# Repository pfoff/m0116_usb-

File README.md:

# m0116_usb
[![CC BY-NC-SA 4.0][cc-by-nc-sa-shield]][cc-by-nc-sa]

**[Deutsch](#deutsch) | [English](#english)**

## Deutsch

### Dieses Projekt ist abgeschlossen und wird nicht mehr aktualisiert.
Wir sind absolute Anfänger und wollen eine Platine für einige unserer M0118
bauen, irgendwann mit Unterstützung für ANSI-Belegung mit AEK-Tastenkappen.
Hilfe und Tipps sind willkommen.

### Wireless-TrackPoint-Revision (Branch `wireless-trackpoint`)

In Arbeit: Der ursprüngliche ATmega32A/V-USB-Controller wird durch einen
gesockelten **nice!nano v2** mit **ZMK** ersetzt, dazu ein PS/2-TrackPoint
und ein LiPo-Akku. Platinenkontur, Schalterpositionen, die 5×18-Matrix und
die Befestigungslöcher bleiben unverändert. Designnotizen, Pinbelegung und
offene Punkte: [docs/wireless-trackpoint-design.md](docs/wireless-trackpoint-design.md)
(englisch).

- `m0116_usb.kicad_sch` – Matrix (unverändert) plus zwei Unterblätter:
  - `controller.kicad_sch` – nice!nano, 3× 74HC595 als Spaltentreiber, LiPo,
    dauerhaft aktiver LDO, TrackPoint-Stecker
  - `usb_daughterboard.kicad_sch` – USB-C-Durchführung auf dem abbrechbaren
    Tab in der hinteren ADB-Aussparung, für Kabelbetrieb und Laden
- `m0116_wireless.kicad_sym` – Projekt-Symbolbibliothek (nice!nano v2)
- `tools/` – Hilfsskripte für das Makefile

Benötigt KiCad 7 (`kicad-cli` und das `pcbnew`-Python-Modul des
System-Pythons). Einmal `git submodule update --init` ausführen, um die
Footprint-Bibliotheken zu holen.

| Befehl | Was er macht |
|---|---|
| `make check` | Netzliste exportieren und die vorgesehenen Verbindungen prüfen |
| `make pcb-update` | Platine ohne GUI aus dem Schaltplan aktualisieren (Pcbnew vorher schließen) |
| `make pcb-check` | Ungeroutete Verbindungen Netz für Netz auflisten |
| `make pdf` | Schaltplan als PDF in `build/` |
| `make gerbers` | Gerber- und Bohrdateien, gezippt in `build/` |
| `make dsn` | Specctra-DSN der Tastenmatrix für Freerouting, in `build/` |
| `make dsn-continue` | DSN mit den vorhandenen Leiterbahnen, Freerouting ergänzt nur die offenen Verbindungen |
| `make clean` | `build/` löschen |

Die Schalter-Footprints sind MX/Alps-Hybride (`MX_Alps_Hybrid:MX-1U-NoLED`);
MX82 ist ein optionaler mittiger MX-Leertastenschalter parallel zum
außermittigen Alps-Leertastenschalter MX73 (nur einen der beiden bestücken).
Die Matrix wird mit Freerouting geroutet: `make dsn`, die DSN routen, dann
ersetzt `/usr/bin/python3 tools/import_ses.py <board> <datei.ses>` die
Leiterbahnen aller Netze aus der Session. Bei einem Teilergebnis
`make dsn-continue` ausführen (GND wird dort als Leiterbahn geroutet, damit
Inseln der Massefläche keine offenen Pads verstecken), routen und erneut
importieren; `/usr/bin/python3 tools/stitch_gnd.py <board>` setzt Vias von
GND-Inseln zur Hauptfläche, wo sich beide Lagen überlappen. Die exportierte
Kontur wird um 0,35 mm verkleinert und die Bohrungen vergrößert, weil
Freerouting nur 0,2 mm Abstand zur Kante hält und KiCad 0,5 mm prüft. Die
Netze der USB-Tochterplatine fehlen in der DSN (enge USB-C-Pads) und werden
von Hand geroutet. Die Frage von Freerouting, eine `.rules`-Datei zu
importieren, mit „Nein“ beantworten: Sie überschreibt die Regeln der neuen
DSN.

#### TKL-Variante (ohne Ziffernblock)

`m0116_tkl.*` wird per Skript aus der großen Platine erzeugt, Änderungen
lassen sich also übertragen: `make tkl-sch` erzeugt die Schaltpläne neu,
`make tkl-pcb` baut die Platine neu (überschreibt `m0116_tkl.kicad_pcb`).
Die anderen Targets nehmen `PROJECT=m0116_tkl`. Die Platine endet nach
Backspace/Return/Pfeiltasten mit der originalen rechten Kontur, um 94,43 mm
nach links verschoben; U4/C5 entfallen (14 Spalten), die rechte
Plattenschraube wandert mit der Kontur und muss in die gekürzte Platte
gebohrt werden.

`make pcb-update` platziert neue Footprints nur beim ersten Anlegen nach
`tools/placement.json`, manuelle Platzierung in Pcbnew bleibt also erhalten.

Stand: Schaltplan fertig (ERC sauber). Die TKL-Platine ist bis auf zwei
Verbindungen autogeroutet; die große Platine muss noch neu geroutet werden.
Der Tab der Tochterplatine muss angepasst werden, sobald die hintere
ADB-Aussparung des Gehäuses ausgemessen ist. Offene Schritte, für
KiCad-Einsteiger beschrieben: [TODO.md](TODO.md) (englisch).

### Originaldesign

Die folgenden Abschnitte beschreiben das ursprüngliche Design.

QMK-kompatible Drop-in-Ersatzplatine für den Apple M0116. Die Platine ist
komplett mit THT-Bauteilen aufgebaut, um einen etwas „vintage“ Look zu
behalten, und verwendet den ATmega32A im 40-poligen DIP-Gehäuse. (Hinweis
der Wireless-Revision: Der Controller sitzt in der Leiste hinter der
Zahlenreihe; die Bemerkung zur Leertaste in der englischen Fassung stammt
aus dem M0110a-Projekt.)

Stückliste (Partslist) und Bilder: siehe unten im englischen Teil, die
Tabelle ist sprachunabhängig.

## English
### This project is completed and will not get updated anymore.
We are complete beginners and want to build a pcb for some of our m0118s, eventually with support for ansi keymap, by using some aek keycaps. 
Any help or tips appreciated

### Wireless TrackPoint revision (branch `wireless-trackpoint`)

Work in progress: the original ATmega32A/V-USB controller is replaced by a
socketed **nice!nano v2** running **ZMK**, with a PS/2 TrackPoint and LiPo
battery. Board outline, switch positions, the 5x18 matrix and the mounting
holes stay unchanged. Design notes, pin assignment and open points:
[docs/wireless-trackpoint-design.md](docs/wireless-trackpoint-design.md).

- `m0116_usb.kicad_sch` - matrix (unchanged) plus two sub-sheets:
  - `controller.kicad_sch` - nice!nano, 3x 74HC595 column drivers, LiPo,
    always-on LDO, TrackPoint header
  - `usb_daughterboard.kicad_sch` - USB-C pass-through on the break-off tab
    in the rear ADB cut-out, for wired use and charging
- `m0116_wireless.kicad_sym` - project symbol library (nice!nano v2)
- `tools/` - helper scripts used by the Makefile

Requires KiCad 7 (`kicad-cli` and the `pcbnew` Python module of the system
Python). Run `git submodule update --init` once to fetch the footprint
libraries.

| Command | What it does |
|---|---|
| `make check` | Export the netlist and verify the intended connections |
| `make pcb-update` | Update the PCB from the schematic without the GUI (close Pcbnew first) |
| `make pcb-check` | List unrouted connections net by net |
| `make pdf` | Schematic as PDF in `build/` |
| `make gerbers` | Gerber and drill files, zipped in `build/` |
| `make dsn` | Specctra DSN of the key matrix for Freerouting, in `build/` |
| `make dsn-continue` | DSN that keeps the existing tracks, so Freerouting only completes open connections |
| `make clean` | Remove `build/` |

Switch footprints are MX/Alps hybrids (`MX_Alps_Hybrid:MX-1U-NoLED`); MX82 is
an optional centred MX spacebar switch in parallel with the off-centre Alps
spacebar switch MX73. The matrix is routed with Freerouting: `make dsn`, route
the DSN, then `/usr/bin/python3 tools/import_ses.py <board> <file.ses>`
replaces the tracks of every net in the session. For a partial result run
`make dsn-continue` (GND is routed as tracks there, so pour islands cannot
hide open pads), route that and import again;
`/usr/bin/python3 tools/stitch_gnd.py <board>` adds vias from GND pour islands
to the main pour where both layers overlap. The exported outline is
shrunk and the holes enlarged by 0.35 mm, because Freerouting keeps only
0.2 mm to the edge and KiCad checks 0.5 mm. The USB daughterboard nets are
left out of the DSN (tight USB-C pads), route them by hand. When Freerouting
asks whether to import a `.rules` file, answer "No": it would override the
rules of the new DSN.

#### TKL variant (no keypad)

`m0116_tkl.*` is derived from the full board by scripts, so changes to the
full board can be carried over: `make tkl-sch` regenerates the schematics,
`make tkl-pcb` rebuilds the PCB (overwrites `m0116_tkl.kicad_pcb`). Other
targets take `PROJECT=m0116_tkl`. The board ends after Backspace/Return/arrows
with the original right-hand contour moved 94.43 mm left; U4/C5 are dropped
(14 columns), the right plate screw moves with the contour and has to be
drilled into the cut-down plate.

`make pcb-update` places new footprints according to `tools/placement.json`
only when they are first created, so manual placement in Pcbnew is kept.

Status: schematic done (ERC clean). The TKL board is autorouted except for
two connections; the full board still has to be rerouted. The daughterboard
tab has to be resized once the rear ADB cut-out of the case is measured.
Open steps, written for KiCad beginners: [TODO.md](TODO.md).

The rest of this README describes the original design.

### QMK compatible drop-in replacement PCB for the Apple M0116
The PCB is built entirely with THT parts to keep a somewhat "vintage" look to it and it uses the fullsize 40-pin DIP package ATmega32A.
The controller is placed in the exact same location as the one on the original PCB meaning that it can be accessed through the plate cutout under the spacebar.
(Note from the wireless revision: on this board the controller actually sits in the strip behind the number row; the spacebar remark was inherited from the M0110a project.)

### Partslist
 |Count|Part|
 |-|-|
 |1|ATmega32A 40 pin DIP (32L works too)|
 |1|40 pin DIP socket (optional but highly recommended)|
 |1|2x3 pin header 2.54mm (for ISP flashing)|
 |1|JST PH 2mm 4pin connector + cable|
 |1|mini usb port|
 |1|500 mA polyfuse|
 |2|6mm momentary push buttons|
 |1|16 MHz quarz crystal|
 |1|4.7 uF electrolytic capacitor|
 |2|100 nF ceramic disk capacitor|
 |2|22 pF ceramic disk capacitor|
 |1|10 kΩ resistor|
 |2|68 Ω resistor|
 |1|1.5 kΩ resistor|
 |2|3.6 V zener diode (DO-35 BZX55C3V6)|
 |81|universal switching diode (DO-35 1N4148)|

#### Some pictures of the first finished PCB

## Lizenz / License

Dieses Werk ist lizenziert unter einer / This work is licensed under a
[Creative Commons Attribution-NonCommercial-ShareAlike 4.0 International License][cc-by-nc-sa].

[![CC BY-NC-SA 4.0][cc-by-nc-sa-image]][cc-by-nc-sa]

[cc-by-nc-sa]: http://creativecommons.org/licenses/by-nc-sa/4.0/
[cc-by-nc-sa-image]: https://licensebuttons.net/l/by-nc-sa/4.0/88x31.png
[cc-by-nc-sa-shield]: https://img.shields.io/badge/License-CC%20BY--NC--SA%204.0-lightgrey.svg

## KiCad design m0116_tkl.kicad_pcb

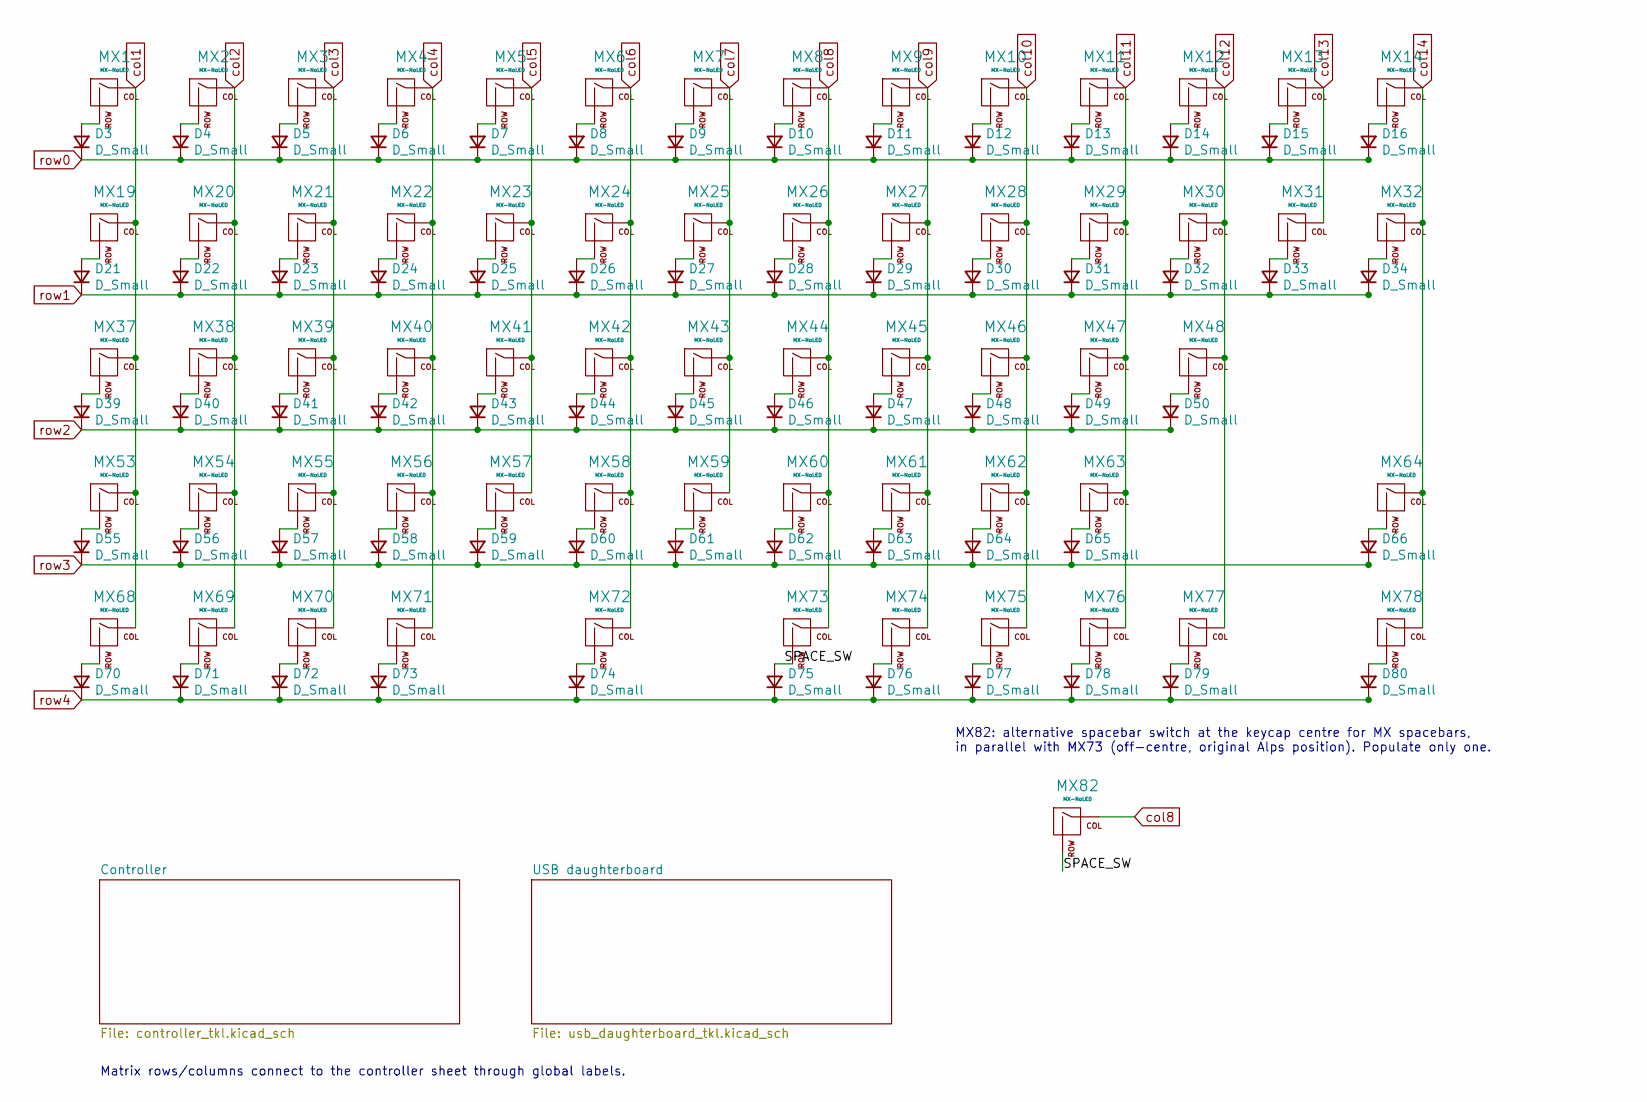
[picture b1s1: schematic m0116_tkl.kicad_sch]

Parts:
D3, D4, D5, D6, D7, D8, D9, D10, D11, D12, D13, D14, D15, D16, D21, D22, D23, D24, D25, D26, D27, D28, D29, D30, D31, D32, D33, D34, D39, D40, D41, D42, D43, D44, D45, D46, D47, D48, D49, D50, D55, D56, D57, D58, D59, D60, D61, D62, D63, D64, D65, D66, D70, D71, D72, D73, D74, D75, D76, D77, D78, D79, D80: D_Small; D_DO-35_SOD27_P7.62mm_Horizontal
MX1, MX2, MX3, MX4, MX5, MX6, MX7, MX8, MX9, MX10, MX11, MX12, MX13, MX14, MX19, MX20, MX21, MX22, MX23, MX24, MX25, MX26, MX27, MX28, MX29, MX30, MX31, MX32, MX37, MX38, MX39, MX40, MX41, MX42, MX43, MX44, MX45, MX46, MX47, MX48, MX53, MX54, MX55, MX56, MX57, MX58, MX59, MX60, MX61, MX62, MX63, MX64, MX68, MX69, MX70, MX71, MX72, MX73, MX74, MX75, MX76, MX77, MX78, MX82: MX-NoLED; MX-1U-NoLED

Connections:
/SPACE_SW: D75.2 (A), MX73.2 (ROW), MX82.2 (ROW)
unnamed: D3.2 (A), MX1.2 (ROW)
unnamed: D4.2 (A), MX2.2 (ROW)
unnamed: D5.2 (A), MX3.2 (ROW)
unnamed: D6.2 (A), MX4.2 (ROW)
unnamed: D7.2 (A), MX5.2 (ROW)
unnamed: D8.2 (A), MX6.2 (ROW)
unnamed: D9.2 (A), MX7.2 (ROW)
unnamed: D10.2 (A), MX8.2 (ROW)
unnamed: D11.2 (A), MX9.2 (ROW)
unnamed: D12.2 (A), MX10.2 (ROW)
unnamed: D13.2 (A), MX11.2 (ROW)
unnamed: D14.2 (A), MX12.2 (ROW)
unnamed: D15.2 (A), MX13.2 (ROW)
unnamed: D16.2 (A), MX14.2 (ROW)
unnamed: D21.2 (A), MX19.2 (ROW)
unnamed: D22.2 (A), MX20.2 (ROW)
unnamed: D23.2 (A), MX21.2 (ROW)
unnamed: D24.2 (A), MX22.2 (ROW)
unnamed: D25.2 (A), MX23.2 (ROW)
unnamed: D26.2 (A), MX24.2 (ROW)
unnamed: D27.2 (A), MX25.2 (ROW)
unnamed: D28.2 (A), MX26.2 (ROW)
unnamed: D29.2 (A), MX27.2 (ROW)
unnamed: D30.2 (A), MX28.2 (ROW)
unnamed: D31.2 (A), MX29.2 (ROW)
unnamed: D32.2 (A), MX30.2 (ROW)
unnamed: D33.2 (A), MX31.2 (ROW)
unnamed: D34.2 (A), MX32.2 (ROW)
unnamed: D39.2 (A), MX37.2 (ROW)
unnamed: D40.2 (A), MX38.2 (ROW)
unnamed: D41.2 (A), MX39.2 (ROW)
unnamed: D42.2 (A), MX40.2 (ROW)
unnamed: D43.2 (A), MX41.2 (ROW)
unnamed: D44.2 (A), MX42.2 (ROW)
unnamed: D45.2 (A), MX43.2 (ROW)
unnamed: D46.2 (A), MX44.2 (ROW)
unnamed: D47.2 (A), MX45.2 (ROW)
unnamed: D48.2 (A), MX46.2 (ROW)
unnamed: D49.2 (A), MX47.2 (ROW)
unnamed: D50.2 (A), MX48.2 (ROW)
unnamed: D55.2 (A), MX53.2 (ROW)
unnamed: D56.2 (A), MX54.2 (ROW)
unnamed: D57.2 (A), MX55.2 (ROW)
unnamed: D58.2 (A), MX56.2 (ROW)
unnamed: D59.2 (A), MX57.2 (ROW)
unnamed: D60.2 (A), MX58.2 (ROW)
unnamed: D61.2 (A), MX59.2 (ROW)
unnamed: D62.2 (A), MX60.2 (ROW)
unnamed: D63.2 (A), MX61.2 (ROW)
unnamed: D64.2 (A), MX62.2 (ROW)
unnamed: D65.2 (A), MX63.2 (ROW)
unnamed: D66.2 (A), MX64.2 (ROW)
unnamed: D70.2 (A), MX68.2 (ROW)
unnamed: D71.2 (A), MX69.2 (ROW)
unnamed: D72.2 (A), MX70.2 (ROW)
unnamed: D73.2 (A), MX71.2 (ROW)
unnamed: D74.2 (A), MX72.2 (ROW)
unnamed: D76.2 (A), MX74.2 (ROW)
unnamed: D77.2 (A), MX75.2 (ROW)
unnamed: D78.2 (A), MX76.2 (ROW)
unnamed: D79.2 (A), MX77.2 (ROW)
unnamed: D80.2 (A), MX78.2 (ROW)
col1: MX1.1 (COL), MX19.1 (COL), MX37.1 (COL), MX53.1 (COL), MX68.1 (COL); also elsewhere on the board
col2: MX2.1 (COL), MX20.1 (COL), MX38.1 (COL), MX54.1 (COL), MX69.1 (COL); also elsewhere on the board
col3: MX3.1 (COL), MX21.1 (COL), MX39.1 (COL), MX55.1 (COL), MX70.1 (COL); also elsewhere on the board
col4: MX4.1 (COL), MX22.1 (COL), MX40.1 (COL), MX56.1 (COL), MX71.1 (COL); also elsewhere on the board
col5: MX5.1 (COL), MX23.1 (COL), MX41.1 (COL), MX57.1 (COL); also elsewhere on the board
col6: MX6.1 (COL), MX24.1 (COL), MX42.1 (COL), MX58.1 (COL), MX72.1 (COL); also elsewhere on the board
col7: MX7.1 (COL), MX25.1 (COL), MX43.1 (COL), MX59.1 (COL); also elsewhere on the board
col8: MX8.1 (COL), MX26.1 (COL), MX44.1 (COL), MX60.1 (COL), MX73.1 (COL), MX82.1 (COL); also elsewhere on the board
col9: MX9.1 (COL), MX27.1 (COL), MX45.1 (COL), MX61.1 (COL), MX74.1 (COL); also elsewhere on the board
col10: MX10.1 (COL), MX28.1 (COL), MX46.1 (COL), MX62.1 (COL), MX75.1 (COL); also elsewhere on the board
col11: MX11.1 (COL), MX29.1 (COL), MX47.1 (COL), MX63.1 (COL), MX76.1 (COL); also elsewhere on the board
col12: MX12.1 (COL), MX30.1 (COL), MX48.1 (COL), MX77.1 (COL); also elsewhere on the board
col13: MX13.1 (COL), MX31.1 (COL); also elsewhere on the board
col14: MX14.1 (COL), MX32.1 (COL), MX64.1 (COL), MX78.1 (COL); also elsewhere on the board
row0: D3.1 (K), D4.1 (K), D5.1 (K), D6.1 (K), D7.1 (K), D8.1 (K), D9.1 (K), D10.1 (K), D11.1 (K), D12.1 (K), D13.1 (K), D14.1 (K), D15.1 (K), D16.1 (K); also elsewhere on the board
row1: D21.1 (K), D22.1 (K), D23.1 (K), D24.1 (K), D25.1 (K), D26.1 (K), D27.1 (K), D28.1 (K), D29.1 (K), D30.1 (K), D31.1 (K), D32.1 (K), D33.1 (K), D34.1 (K); also elsewhere on the board
row2: D39.1 (K), D40.1 (K), D41.1 (K), D42.1 (K), D43.1 (K), D44.1 (K), D45.1 (K), D46.1 (K), D47.1 (K), D48.1 (K), D49.1 (K), D50.1 (K); also elsewhere on the board
row3: D55.1 (K), D56.1 (K), D57.1 (K), D58.1 (K), D59.1 (K), D60.1 (K), D61.1 (K), D62.1 (K), D63.1 (K), D64.1 (K), D65.1 (K), D66.1 (K); also elsewhere on the board
row4: D70.1 (K), D71.1 (K), D72.1 (K), D73.1 (K), D74.1 (K), D75.1 (K), D76.1 (K), D77.1 (K), D78.1 (K), D79.1 (K), D80.1 (K); also elsewhere on the board

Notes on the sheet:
Matrix rows/columns connect to the controller sheet through global labels.
MX82: alternative spacebar switch at the keycap centre for MX spacebars, in parallel with MX73 (off-centre, original Alps position). Populate only one.

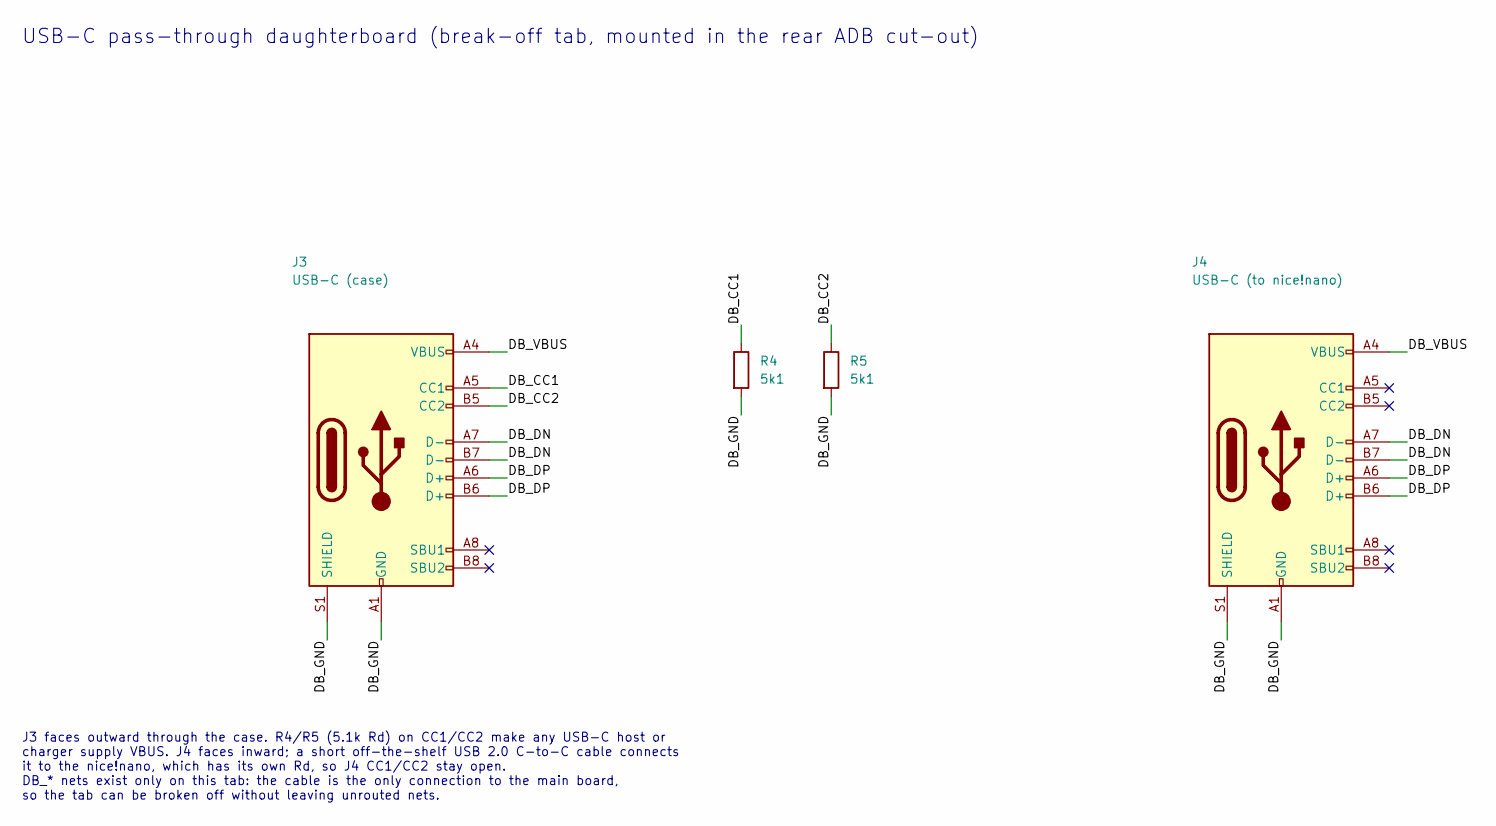
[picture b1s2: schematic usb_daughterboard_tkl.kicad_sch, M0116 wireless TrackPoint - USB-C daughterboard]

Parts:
J3: USB-C (case); USB_C_Receptacle_GCT_USB4085
J4: USB-C (to nice!nano); USB_C_Receptacle_GCT_USB4085
R4, R5: 5k1; R_Axial_DIN0207_L6.3mm_D2.5mm_P2.54mm_Vertical

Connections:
/USB daughterboard/DB_CC1: J3.A5 (CC1), R4.1
/USB daughterboard/DB_CC2: J3.B5 (CC2), R5.1
/USB daughterboard/DB_DN: J3.A7 (D-), J3.B7 (D-), J4.A7 (D-), J4.B7 (D-)
/USB daughterboard/DB_DP: J3.A6 (D+), J3.B6 (D+), J4.A6 (D+), J4.B6 (D+)
/USB daughterboard/DB_GND: J3.A1 (GND), J3.A12 (GND), J3.B1 (GND), J3.B12 (GND), J3.S1 (SHIELD), J4.A1 (GND), J4.A12 (GND), J4.B1 (GND), J4.B12 (GND), J4.S1 (SHIELD), R4.2, R5.2
/USB daughterboard/DB_VBUS: J3.A4 (VBUS), J3.A9 (VBUS), J3.B4 (VBUS), J3.B9 (VBUS), J4.A4 (VBUS), J4.A9 (VBUS), J4.B4 (VBUS), J4.B9 (VBUS)

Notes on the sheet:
USB-C pass-through daughterboard (break-off tab, mounted in the rear ADB cut-out)
J3 faces outward through the case. R4/R5 (5.1k Rd) on CC1/CC2 make any USB-C host or charger supply VBUS. J4 faces inward; a short off-the-shelf USB 2.0 C-to-C cable connects it to the nice!nano, which has its own Rd, so J4 CC1/CC2 stay open. DB_* nets exist only on this tab: the cable is the only 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

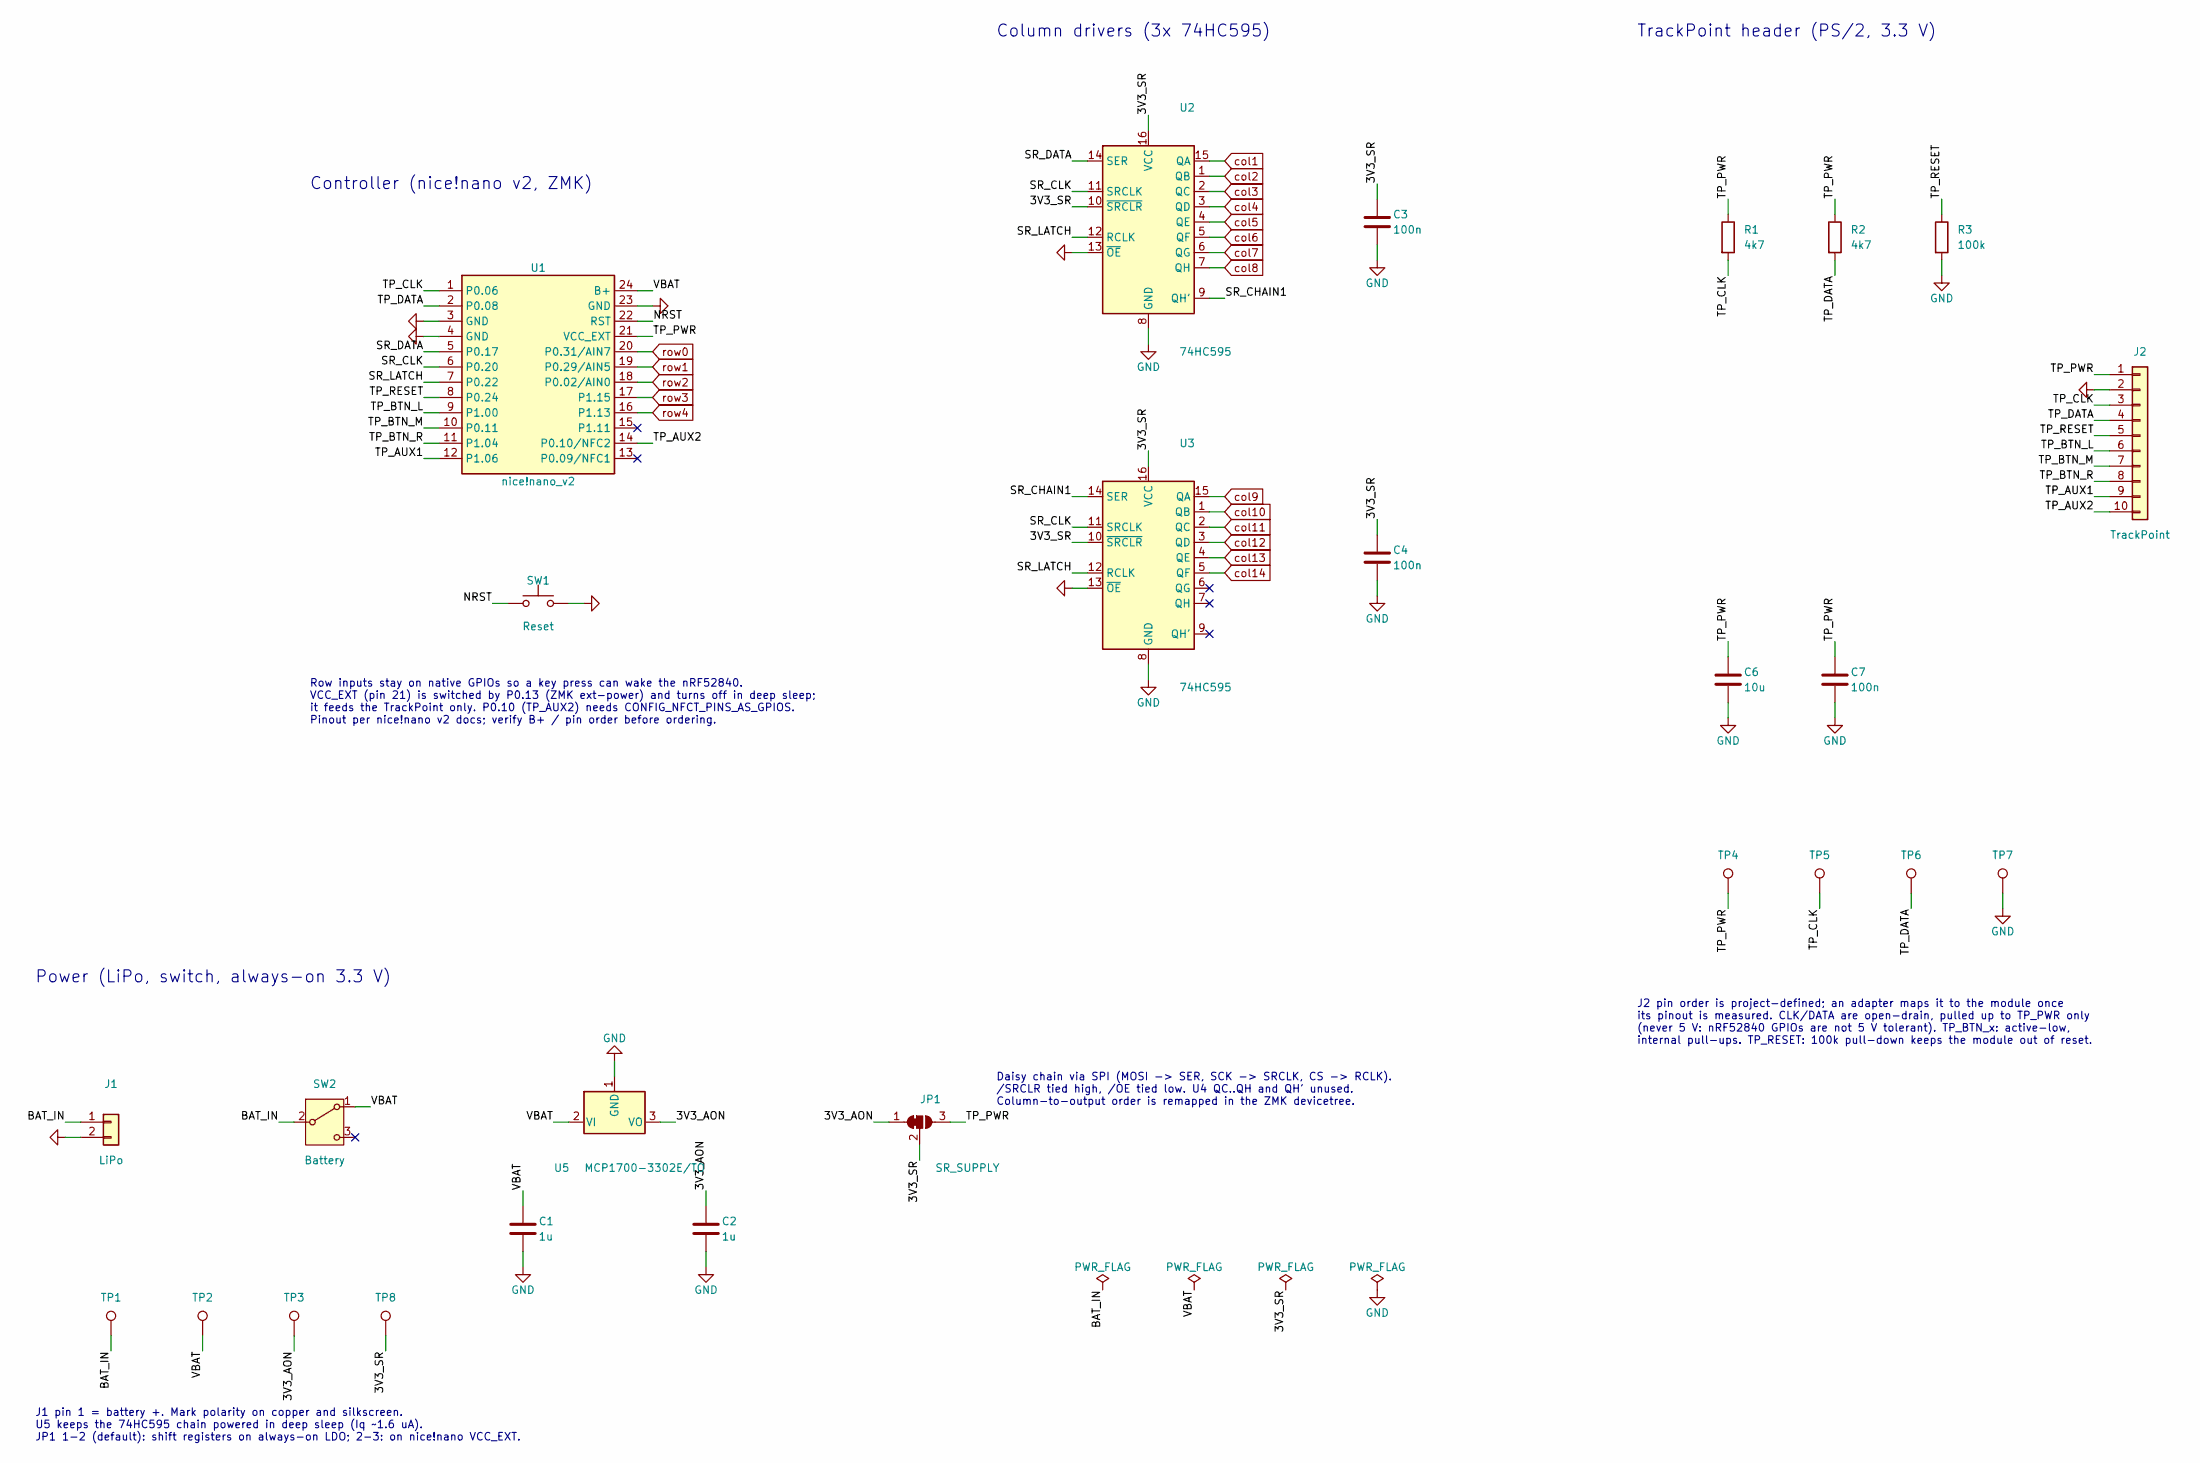
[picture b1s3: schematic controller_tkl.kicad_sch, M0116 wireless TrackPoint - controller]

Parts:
C1, C2: 1u; C_Disc_D3.0mm_W2.0mm_P2.50mm
C3, C4, C7: 100n; C_Disc_D3.0mm_W2.0mm_P2.50mm
C6: 10u; C_Disc_D5.0mm_W2.5mm_P5.00mm
J1: LiPo; JST_PH_S2B-PH-K_1x02_P2.00mm_Horizontal
J2: TrackPoint; PinHeader_1x10_P2.54mm_Vertical
JP1: SR_SUPPLY; SolderJumper-3_P1.3mm_Bridged12_RoundedPad1.0x1.5mm_NumberL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
R1, R2: 4k7; R_Axial_DIN0207_L6.3mm_D2.5mm_P10.16mm_Horizontal
R3: 100k; R_Axial_DIN0207_L6.3mm_D2.5mm_P10.16mm_Horizontal
SW1: Reset; SW_PUSH_6mm
SW2: Battery; SW_Slide_SPDT_Angled_CK_OS102011MA1Q
TP1: BAT_IN; TestPoint_THTPad_D1.5mm_Drill0.7mm
TP2: VBAT; TestPoint_THTPad_D1.5mm_Drill0.7mm
TP3: 3V3_AON; TestPoint_THTPad_D1.5mm_Drill0.7mm
TP4: TP_PWR; TestPoint_THTPad_D1.5mm_Drill0.7mm
TP5: TP_CLK; TestPoint_THTPad_D1.5mm_Drill0.7mm
TP6: TP_DATA; TestPoint_THTPad_D1.5mm_Drill0.7mm
TP7: GND; TestPoint_THTPad_D1.5mm_Drill0.7mm
TP8: 3V3_SR; TestPoint_THTPad_D1.5mm_Drill0.7mm
U1: nice!nano_v2; DIP-24_W15.24mm_Socket
U2, U3: 74HC595; DIP-16_W7.62mm_Socket
U5: MCP1700-3302E/TO; TO-92_Inline

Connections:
/Controller/3V3_AON: C2.1, JP1.1 (A), TP3.1, U5.3 (VO)
/Controller/3V3_SR: C3.1, C4.1, JP1.2 (C), TP8.1, U2.10 (~SRCLR), U2.16 (VCC), U3.10 (~SRCLR), U3.16 (VCC)
/Controller/BAT_IN: J1.1, SW2.2 (B), TP1.1
/Controller/NRST: SW1.1, U1.22 (RST)
/Controller/SR_CHAIN1: U2.9 (QH'), U3.14 (SER)
/Controller/SR_CLK: U1.6 (P0.20), U2.11 (SRCLK), U3.11 (SRCLK)
/Controller/SR_DATA: U1.5 (P0.17), U2.14 (SER)
/Controller/SR_LATCH: U1.7 (P0.22), U2.12 (RCLK), U3.12 (RCLK)
/Controller/TP_AUX1: J2.9, U1.12 (P1.06)
/Controller/TP_AUX2: J2.10, U1.14 (P0.10/NFC2)
/Controller/TP_BTN_L: J2.6, U1.9 (P1.00)
/Controller/TP_BTN_M: J2.7, U1.10 (P0.11)
/Controller/TP_BTN_R: J2.8, U1.11 (P1.04)
/Controller/TP_CLK: J2.3, R1.2, TP5.1, U1.1 (P0.06)
/Controller/TP_DATA: J2.4, R2.2, TP6.1, U1.2 (P0.08)
/Controller/TP_PWR: C6.1, C7.1, J2.1, JP1.3 (B), R1.1, R2.1, TP4.1, U1.21 (VCC_EXT)
/Controller/TP_RESET: J2.5, R3.1, U1.8 (P0.24)
/Controller/VBAT: C1.1, SW2.1 (A), TP2.1, U1.24 (B+), U5.2 (VI)
GND: C1.2, C2.2, C3.2, C4.2, C6.2, C7.2, J1.2, J2.2, R3.2, SW1.2, TP7.1, U1.3 (GND), U1.4 (GND), U1.23 (GND), U2.8 (GND), U2.13 (~OE), U3.8 (GND), U3.13 (~OE), U5.1 (GND)
col1: U2.15 (QA); also elsewhere on the board
col2: U2.1 (QB); also elsewhere on the board
col3: U2.2 (QC); also elsewhere on the board
col4: U2.3 (QD); also elsewhere on the board
col5: U2.4 (QE); also elsewhere on the board
col6: U2.5 (QF); also elsewhere on the board
col7: U2.6 (QG); also elsewhere on the board
col8: U2.7 (QH); also elsewhere on the board
col9: U3.15 (QA); also elsewhere on the board
col10: U3.1 (QB); also elsewhere on the board
col11: U3.2 (QC); also elsewhere on the board
col12: U3.3 (QD); also elsewhere on the board
col13: U3.4 (QE); also elsewhere on the board
col14: U3.5 (QF); also elsewhere on the board
row0: U1.20 (P0.31/AIN7); also elsewhere on the board
row1: U1.19 (P0.29/AIN5); also elsewhere on the board
row2: U1.18 (P0.02/AIN0); also elsewhere on the board
row3: U1.17 (P1.15); also elsewhere on the board
row4: U1.16 (P1.13); also elsewhere on the board

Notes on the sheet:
J1 pin 1 = battery +. Mark polarity on copper and silkscreen. U5 keeps the 74HC595 chain powered in deep sleep (Iq ~1.6 uA). JP1 1-2 (default): shift registers on always-on LDO; 2-3: on nice!nano VCC_EXT.
Row inputs stay on native GPIOs so a key press can wake the nRF52840. VCC_EXT (pin 21) is switched by P0.13 (ZMK ext-power) and turns off in deep sleep; it feeds the TrackPoint only. P0.10 (TP_AUX2) needs CONFIG_NFCT_PINS_AS_GPIOS. Pinout per nice!nano v2 docs; verify B+ / pin order before ordering.
Column drivers (3x 74HC595)
Controller (nice!nano v2, ZMK)
Power (LiPo, switch, always-on 3.3 V)
Daisy chain via SPI (MOSI -> SER, SCK -> SRCLK, CS -> RCLK). /SRCLR tied high, /OE tied low. U4 QC..QH and QH' unused. Column-to-output order is remapped in the ZMK devicetree.
TrackPoint header (PS/2, 3.3 V)
J2 pin order is project-defined; an adapter maps it to the module once its pinout is measured. CLK/DATA are open-drain, pulled up to TP_PWR only (never 5 V: nRF52840 GPIOs are not 5 V tolerant). TP_BTN_x: active-low, internal pull-ups. TP_RESET: 100k pull-down keeps the module out of reset.

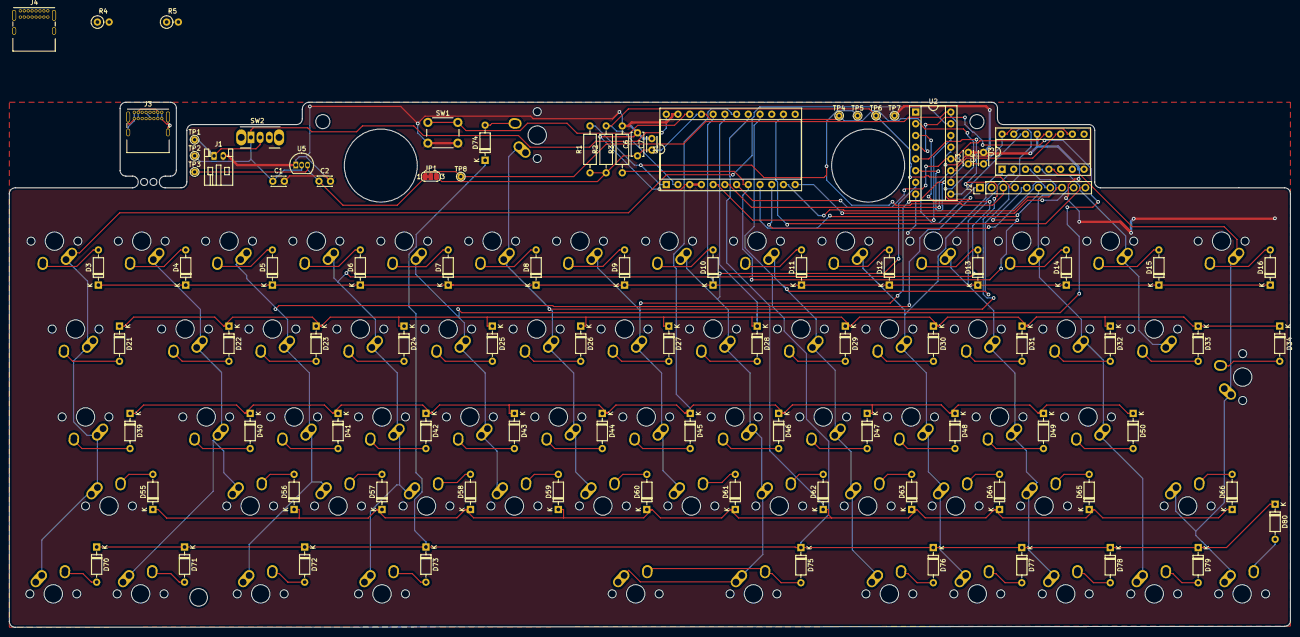
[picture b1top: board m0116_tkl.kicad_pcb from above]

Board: 2 copper layers, 277.7 x 113.8 mm, 157 parts (0 on the bottom side), 107 nets.

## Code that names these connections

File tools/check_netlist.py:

#!/usr/bin/python3
"""Check the schematic netlist against the intended Revision A connections.

Verifies every controller-side pin assignment, that each row/column net
bridges the matrix and the controller, and that no net has a single pin
(except pins explicitly marked no-connect).

Usage: python3 tools/check_netlist.py build/m0116_usb.net [columns]

columns defaults to 18; the TKL variant (no keypad) uses 14 and only U2/U3.
"""
import re
import sys

text = open(sys.argv[1]).read()
COLS = int(sys.argv[2]) if len(sys.argv) > 2 else 18
comps = dict(re.findall(r'\(comp \(ref "([^"]+)"\)\s*\(value "([^"]*)"\)', text))
nets = {}
for chunk in text.split('(net (code ')[1:]:
    name = re.match(r'"\d+"\) \(name "([^"]*)"\)', chunk).group(1)
    nets[name] = sorted(re.findall(r'\(node \(ref "([^"]+)"\) \(pin "([^"]+)"\)', chunk))


def net_of(ref, pin):
    for name, nodes in nets.items():
        if (ref, pin) in nodes:
            return name
    return None


def short(n):
    return n.rsplit("/", 1)[-1]


errors = []
print("components:", len(comps), " nets:", len(nets))
mx = [r for r in comps if r.startswith("MX")]
dio = [r for r in comps if re.fullmatch(r"D\d+", r)]
print("matrix switches:", len(mx), " diodes:", len(dio))

expect = {
    ("U1", "1"): "TP_CLK", ("U1", "2"): "TP_DATA", ("U1", "3"): "GND", ("U1", "4"): "GND",
    ("U1", "5"): "SR_DATA", ("U1", "6"): "SR_CLK", ("U1", "7"): "SR_LATCH", ("U1", "8"): "TP_RESET",
    ("U1", "9"): "TP_BTN_L", ("U1", "10"): "TP_BTN_M", ("U1", "11"): "TP_BTN_R", ("U1", "12"): "TP_AUX1",
    ("U1", "14"): "TP_AUX2", ("U1", "16"): "row4", ("U1", "17"): "row3", ("U1", "18"): "row2",
    ("U1", "19"): "row1", ("U1", "20"): "row0", ("U1", "21"): "TP_PWR", ("U1", "22"): "NRST",
    ("U1", "23"): "GND", ("U1", "24"): "VBAT",
    ("U2", "14"): "SR_DATA", ("U3", "14"): "SR_CHAIN1", ("U2", "9"): "SR_CHAIN1",
    ("U5", "2"): "VBAT", ("U5", "3"): "3V3_AON", ("U5", "1"): "GND",
    ("SW2", "2"): "BAT_IN", ("SW2", "1"): "VBAT", ("J1", "1"): "BAT_IN", ("J1", "2"): "GND",
    ("JP1", "1"): "3V3_AON", ("JP1", "2"): "3V3_SR", ("JP1", "3"): "TP_PWR",
    ("SW1", "1"): "NRST", ("SW1", "2"): "GND",
    ("R1", "1"): "TP_PWR", ("R1", "2"): "TP_CLK", ("R2", "1"): "TP_PWR", ("R2", "2"): "TP_DATA",
    ("R3", "1"): "TP_RESET", ("R3", "2"): "GND",
}
for i, n in enumerate(["TP_PWR", "GND", "TP_CLK", "TP_DATA", "TP_RESET", "TP_BTN_L", "TP_BTN_M",
                       "TP_BTN_R", "TP_AUX1", "TP_AUX2"]):
    expect[("J2", str(i + 1))] = n
qs = ["15", "1", "2", "3", "4", "5", "6", "7"]
if COLS > 16:
    expect.update({("U4", "14"): "SR_CHAIN2", ("U3", "9"): "SR_CHAIN2"})
for u, base in (("U2", 1), ("U3", 9), ("U4", 17)):
    if base > COLS:
        continue
    for pin in ("11",):
        expect[(u, pin)] = "SR_CLK"
    expect[(u, "12")] = "SR_LATCH"
    expect[(u, "10")] = "3V3_SR"
    expect[(u, "16")] = "3V3_SR"
    expect[(u, "13")] = "GND"
    expect[(u, "8")] = "GND"
    for j, q in enumerate(qs):
        if base + j <= COLS:
            expect[(u, q)] = "col%d" % (base + j)
for ref in ("J3", "J4"):
    for pin, want in (("A4", "DB_VBUS"), ("B9", "DB_VBUS"), ("A6", "DB_DP"), ("B6", "DB_DP"),
                      ("A7", "DB_DN"), ("B7", "DB_DN"), ("A1", "DB_GND"), ("S1", "DB_GND")):
        expect[(ref, pin)] = want
expect.update({("J3", "A5"): "DB_CC1", ("J3", "B5"): "DB_CC2", ("R4", "1"): "DB_CC1", ("R5", "1"): "DB_CC2",
               ("R4", "2"): "DB_GND", ("R5", "2"): "DB_GND"})
for (ref, pin), want in expect.items():
    got = net_of(ref, pin)
    if got is None or short(got) != want:
        errors.append("%s.%s: expected %s, got %s" % (ref, pin, want, got))

# every row/col net must reach the matrix AND the controller side
for name, nodes in nets.items():
    s = short(name)
    if re.fullmatch(r"row\d|col\d+", s):
        refs = {r for r, _ in nodes}
        side_matrix = any(r.startswith(("MX", "D")) for r in refs)
        side_ctrl = any(r in ("U1", "U2", "U3", "U4") for r in refs)
        if not (side_matrix and side_ctrl):
            errors.append("net %s not bridging matrix<->controller: %s" % (name, sorted(refs)))
rowcol = sorted(short(n) for n in nets if re.fullmatch(r"row\d|col\d+", short(n)))
print("row/col nets:", len(rowcol))

# single-node nets (excluding intentional NC pins and unconnected-* nets)
for name, nodes in nets.items():
    if len(nodes) == 1 and not name.startswith("unconnected"):
        errors.append("single-node net %s: %s" % (name, nodes))
unconnected = sorted(n for n in nets if n.startswith("unconnected"))
print("unconnected (NC) pins:", len(unconnected))
for n in unconnected:
    print("   ", n)

print("ERRORS:" if errors else "OK: all expected connections present")
for e in errors:
    print("  ", e)
sys.exit(1 if errors else 0)

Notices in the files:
controller_tkl.kicad_sch:
Based on m0116_usb by elmo (CC BY-NC-SA 4.0)
